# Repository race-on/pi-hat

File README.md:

Race On Pi HAT
=====

A Raspberry Pi HAT to control a self-driving car. HAT includes:
1. 3.5A DC-DC converter to power the Pi from a battery (2-3 LiPo cells)
2. 10A H-bridge for DC motor control
3. 3A LDO to power servo at 6V for faster response time
4. Battery alarm when the voltage drops under 6V
5. I2C accelerometer interface
6. Interface for encoders based on the QRE1113 analog line sensor
7. Compatible with Jetson Nano
8. Reverse polarity protection
9. Optimized for Seeed Studio PCBA

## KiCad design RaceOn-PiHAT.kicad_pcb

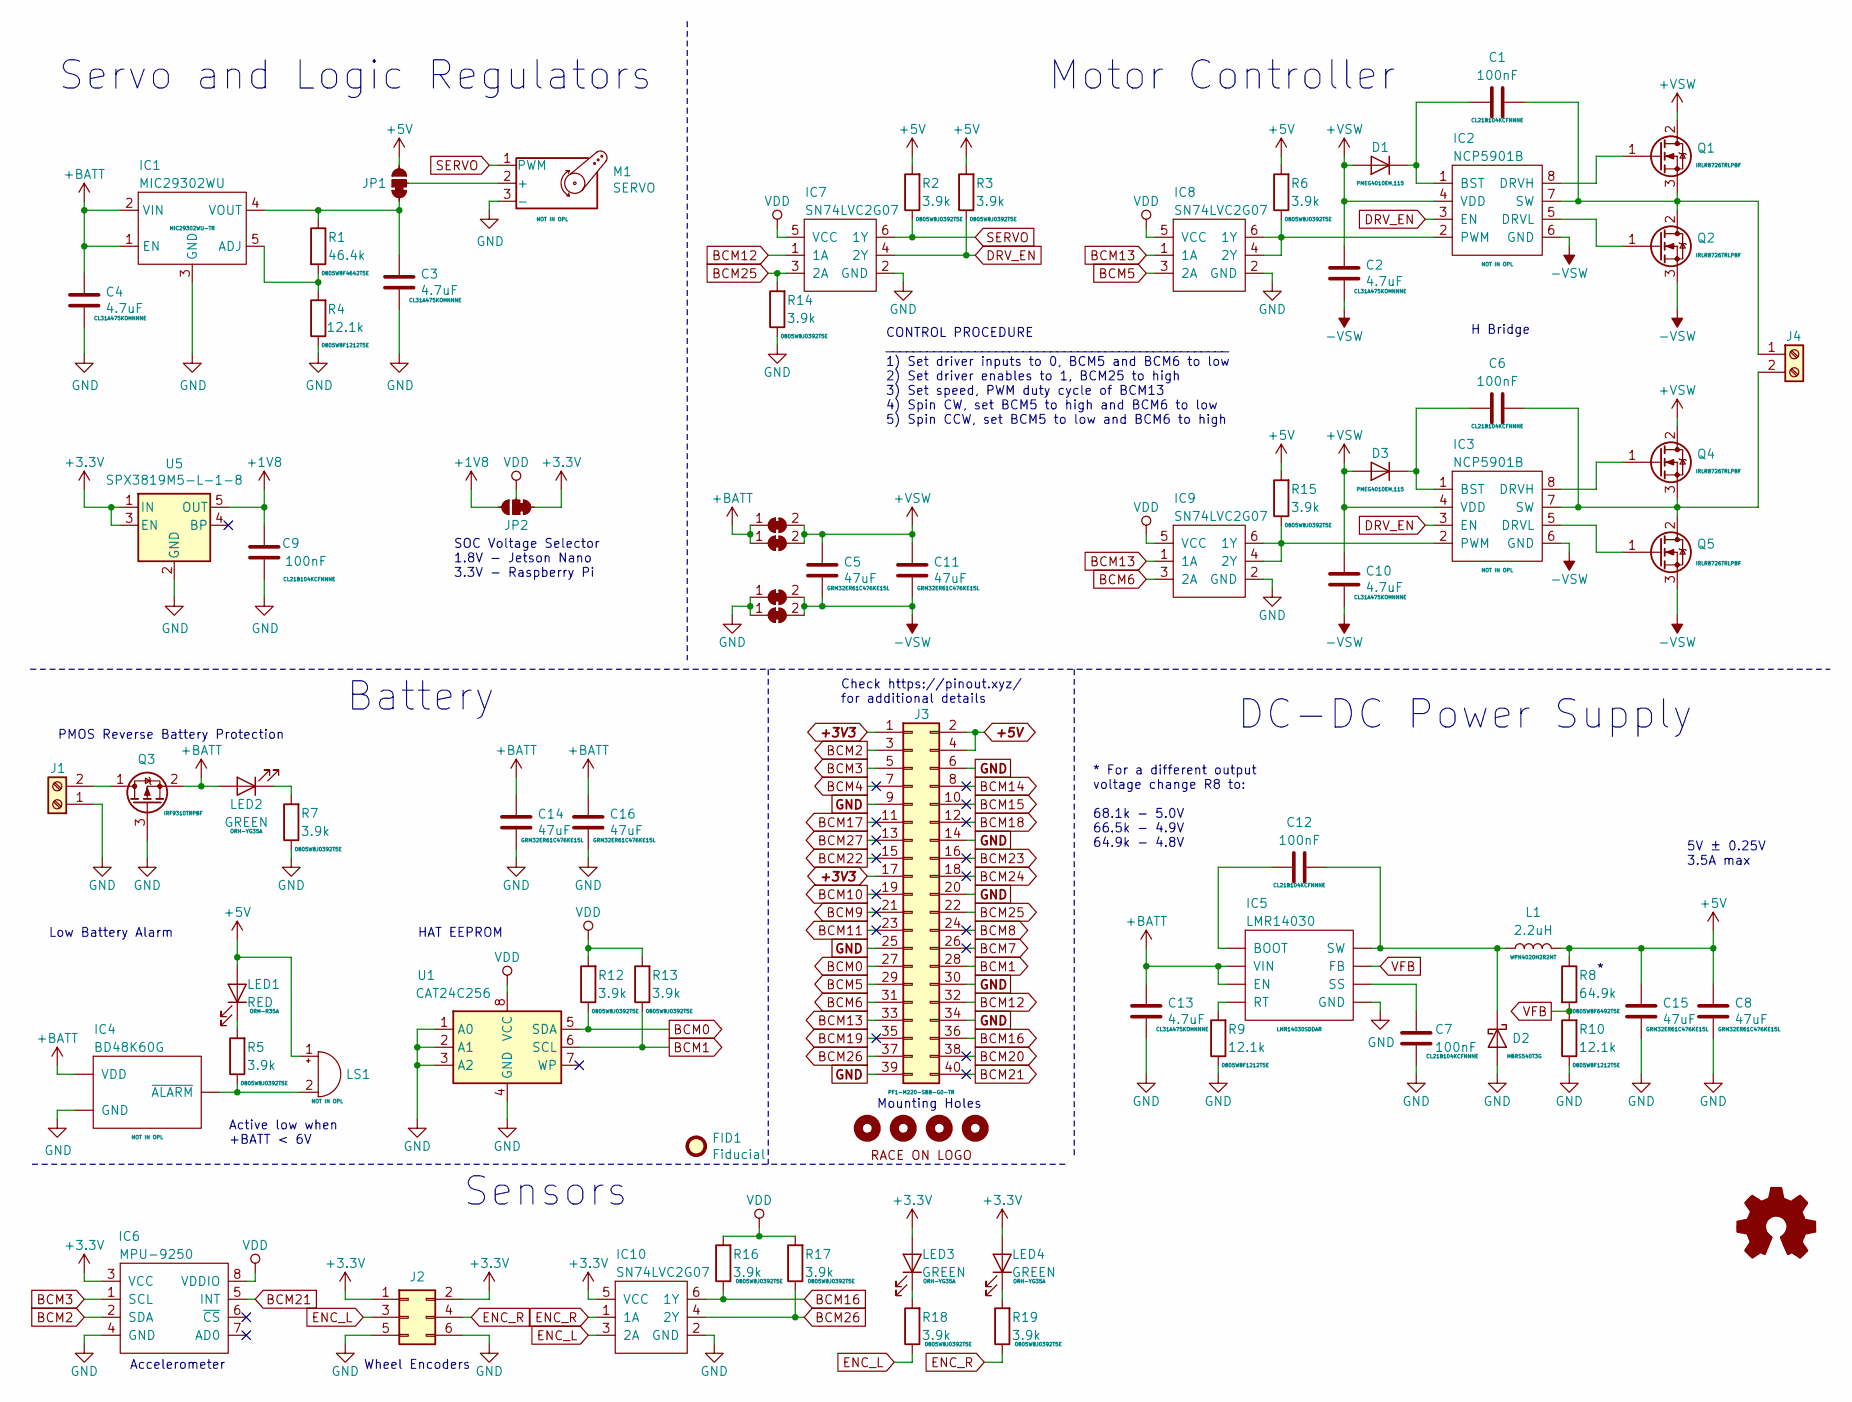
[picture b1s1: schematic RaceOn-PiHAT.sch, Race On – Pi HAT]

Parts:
C1, C6, C7, C9, C12: 100nF; CAPC200X125X95L45M; MPN CL21B104KCFNNNE
C2, C3, C4, C10, C13: 4.7uF; CAPC320X160X180L50M; MPN CL31A475KOHNNNE
C5, C8, C11, C14, C15, C16: 47uF; CAPC320X250X270L60M; MPN GRM32ER61C476KE15L
D1, D3: D; SOD350X160X120L45X62M; MPN PMEG4010EH,115
D2: D_Schottky; DIOM795X590X261L117X305M; MPN MBRS540T3G
FID1: Fiducial; FID1M3
H1, H2, H3, H4: MountingHole; MTGP620H275V8H50
IC1: MIC29302WU; DPAK6P67_587X190L89X29T300X275M; MPN MIC29302WU-TR
IC2, IC3: NCP5901B; SOIC8P127_490X600X175L83X42M; MPN NOT IN OPL
IC4: BD48K60G; SOT23-3P95_280X125L45X40M; MPN NOT IN OPL
IC5: LMR14030; SOIC9P127_490X600X170L83X41T287X202; MPN LMR14030SDDAR
IC6: MPU-9250; PGA28P254C7R4L1840X1127H200
IC7, IC8, IC9, IC10: SN74LVC2G07; SOT23-6P95_280X145L45X37M; MPN SN74LVC2G07DBVR
J1, J4: Screw_Terminal_01x02; TerminalBlock_Phoenix_PT-1,5-2-5.0-H_1x02_P5.00mm_Horizontal; MPN 1935161
J2: Conn_02x03_Odd_Even; HDRV6W65P254_3X2_762X508H900; MPN A2541WV-2x3P
J3: Pi Connector; RHDRV40W64P254_20X2_5120X500H850; MPN PF1-M220-SBB-G0-TR
JP1, JP2: SolderJumper; SJ3B12P10X15
JP3, JP4, JP5, JP6: SolderJumper_2_Bridged; SolderJumper-2_P1.3mm_Bridged_Pad1.0x1.5mm
L1: 2.2uH; INDM400X400X200L95X310M; MPN WPN4020H2R2MT
LED1: RED; LEDC197X125X85L45L; MPN ORH-R35A
LED2, LED3, LED4: GREEN; LEDC197X125X85L45L; MPN ORH-YG35A
LOGO1: RACEON-LOGO; RACEON
LOGO2: Logo_Open_Hardware_Small; OSHW-Logo2_7.3x6mm_SilkScreen
LS1: AI1027TWT5V2R; LSP500W60D980H500; MPN NOT IN OPL
M1: SERVO; HDRV3W64P254_3X1_762X254H854; MPN NOT IN OPL
Q1, Q2, Q4, Q5: IPD50R380CE; DPAK3P460_990X239L160X76T650X546L; MPN IRLR8726TRLPBF
Q3: SQJA37EP1; SOIC8P127_490X600X175L83X42M-TRANZISTOR; MPN IRF9310TRPBF
R1: 46.4k; RESC200X127X65L40M; MPN 0805W8F4642T5E
R2, R3, R5, R6, R7, R12, R13, R14, R15, R16, R17, R18, R19: 3.9k; RESC200X127X65L40M; MPN 0805W8J0392T5E
R4, R9, R10: 12.1k; RESC200X127X65L40M; MPN 0805W8F1212T5E
R8: 64.9k; RESC200X127X65L40M; MPN 0805W8F6492T5E
U1: CAT24C256; SOIC8P127_490X600X175L83X42M; MPN CAT24C256WI-GT3
U5: SPX3819M5-L-1-8; SOT23-5P95_280X145L45X40M; MPN SPX3819M5-L-1-8/TR

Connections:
+1V8: C9.2, JP2.3 (B), U5.5 (OUT)
+5V: C8.2, C15.2, J3.2, J3.4, JP1.3 (B), L1.1, LED1.2 (A), LS1.1 (-), R2.2, R3.2, R6.2, R8.1, R15.2
+BATT: C4.2, C13.2, C14.2, C16.2, IC1.1 (EN), IC1.2 (VIN), IC4.3 (VDD), IC5.2 (VIN), IC5.3 (EN), JP3.1 (A), JP4.1 (A), LED2.2 (A), Q3.2 (S)
+VSW: C2.2, C5.2, C10.2, C11.2, D1.2 (A), D3.2 (A), IC2.4 (VDD), IC3.4 (VDD), JP3.2 (B), JP4.2 (B), Q1.2 (D), Q4.2 (D)
-VSW: C2.1, C5.1, C10.1, C11.1, IC2.6 (GND), IC3.6 (GND), JP5.2 (B), JP6.2 (B), Q2.3 (S), Q5.3 (S)
BCM0: J3.27, R12.1, U1.5 (SDA)
BCM1: J3.28, R13.1, U1.6 (SCL)
BCM2: IC6.2 (SDA), J3.3
BCM3: IC6.1 (SCL), J3.5
BCM4: J3.7
BCM5: IC8.3 (2A), J3.29
BCM6: IC9.3 (2A), J3.31
BCM7: J3.26
BCM8: J3.24
BCM9: J3.21
BCM10: J3.19
BCM11: J3.23
BCM12: IC7.1 (1A), J3.32
BCM13: IC8.1 (1A), IC9.1 (1A), J3.33
BCM14: J3.8
BCM15: J3.10
BCM16: IC10.6 (1Y), J3.36, R16.1
BCM17: J3.11
BCM18: J3.12
BCM19: J3.35
BCM20: J3.38
BCM21: IC6.5 (INT), J3.40
BCM22: J3.15
BCM23: J3.16
BCM24: J3.18
BCM25: IC7.3 (2A), J3.22, R14.2
BCM26: IC10.4 (2Y), J3.37, R17.1
BCM27: J3.13
DRV_EN: IC2.3 (EN), IC3.3 (EN), IC7.4 (2Y), R3.1
ENC_L: IC10.3 (2A), J2.3, R18.1
ENC_R: IC10.1 (1A), J2.4, R19.1
GND: C3.1, C4.1, C7.1, C8.1, C9.1, C13.1, C14.1, C15.1, C16.1, D2.2 (A), IC1.3 (GND), IC1.6 (GND), IC4.1 (GND), IC5.7 (GND), IC5.9 (GND), IC6.4 (GND), IC7.2 (GND), IC8.2 (GND), IC9.2 (GND), IC10.2 (GND), J1.1, J2.5, J2.6, J3.6, J3.9, J3.14, J3.20, J3.25, J3.30, J3.34, J3.39, JP5.1 (A), JP6.1 (A), M1.3 (-), Q3.3 (G), R4.1, R7.1, R9.1, R10.1, R14.1, U1.1 (A0), U1.2 (A1), U1.3 (A2), U1.4 (GND), U5.2 (GND)
unnamed: C1.1, IC2.7 (SW), J4.1, Q1.3 (S), Q2.2 (D)
unnamed: C1.2, D1.1 (K), IC2.1 (BST)
unnamed: C3.2, IC1.4 (VOUT), JP1.1 (A), R1.1
unnamed: C6.1, IC3.7 (SW), J4.2, Q4.3 (S), Q5.2 (D)
unnamed: C6.2, D3.1 (K), IC3.1 (BST)
unnamed: C7.2, IC5.6 (SS)
unnamed: C12.1, D2.1 (K), IC5.8 (SW), L1.2
unnamed: C12.2, IC5.1 (BOOT)
unnamed: IC1.5 (ADJ), R1.2, R4.2
unnamed: IC2.2 (PWM), IC8.4 (2Y), IC8.6 (1Y), R6.1
unnamed: IC2.5 (DRVL), Q2.1 (G)
unnamed: IC2.8 (DRVH), Q1.1 (G)
unnamed: IC3.2 (PWM), IC9.4 (2Y), IC9.6 (1Y), R15.1
unnamed: IC3.5 (DRVL), Q5.1 (G)
unnamed: IC3.8 (DRVH), Q4.1 (G)
unnamed: IC4.2 (~ALARM), LS1.2 (+), R5.1
unnamed: IC5.4 (RT), R9.2
unnamed: J1.2, Q3.1 (D)
unnamed: JP1.2 (C), M1.2 (+)
unnamed: LED1.1 (K), R5.2
unnamed: LED2.1 (K), R7.2
unnamed: LED3.1 (K), R18.2
unnamed: LED4.1 (K), R19.2
SERVO: IC7.6 (1Y), M1.1 (PWM), R2.1
VDD: IC6.8 (VDDIO), IC7.5 (VCC), IC8.5 (VCC), IC9.5 (VCC), JP2.2 (C), R12.2, R13.2, R16.2, R17.2, U1.8 (VCC)
VFB: IC5.5 (FB), R8.2, R10.2

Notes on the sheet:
DC-DC Power Supply
5V ± 0.25V 3.5A max
Motor Controller
Low Battery Alarm
* For a different output voltage change R8 to: 68.1k - 5.0V 66.5k - 4.9V 64.9k - 4.8V
Servo and Logic Regulators
H Bridge
SOC Voltage Selector 1.8V - Jetson Nano 3.3V - Raspberry Pi
Sensors
Accelerometer
Wheel Encoders
Check https://pinout.xyz/ for additional details
Mounting Holes
PMOS Reverse Battery Protection
HAT EEPROM
CONTROL PROCEDURE __________________________________________________ 1) Set driver inputs to 0, BCM5 and BCM6 to low 2) Set driver enables to 1, BCM25 to high 3) Set speed, PWM duty cycle of BCM13 4) Spin CW, set BCM5 to high and BCM6 to low 5) Spin CCW, set BCM5 to low and BCM6 to high
Battery
Active low when +BATT < 6V

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
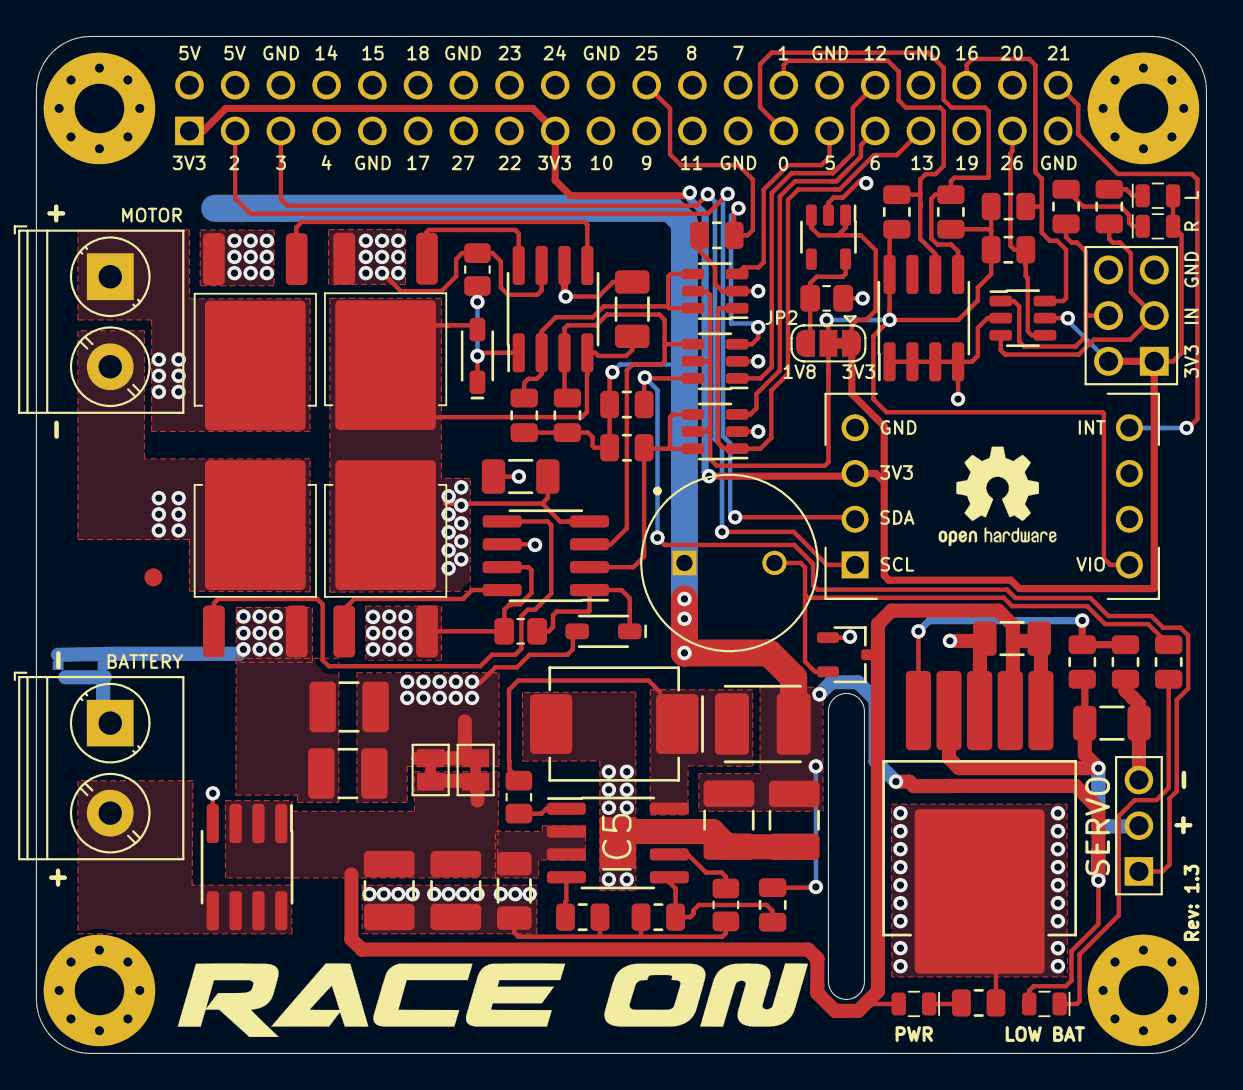
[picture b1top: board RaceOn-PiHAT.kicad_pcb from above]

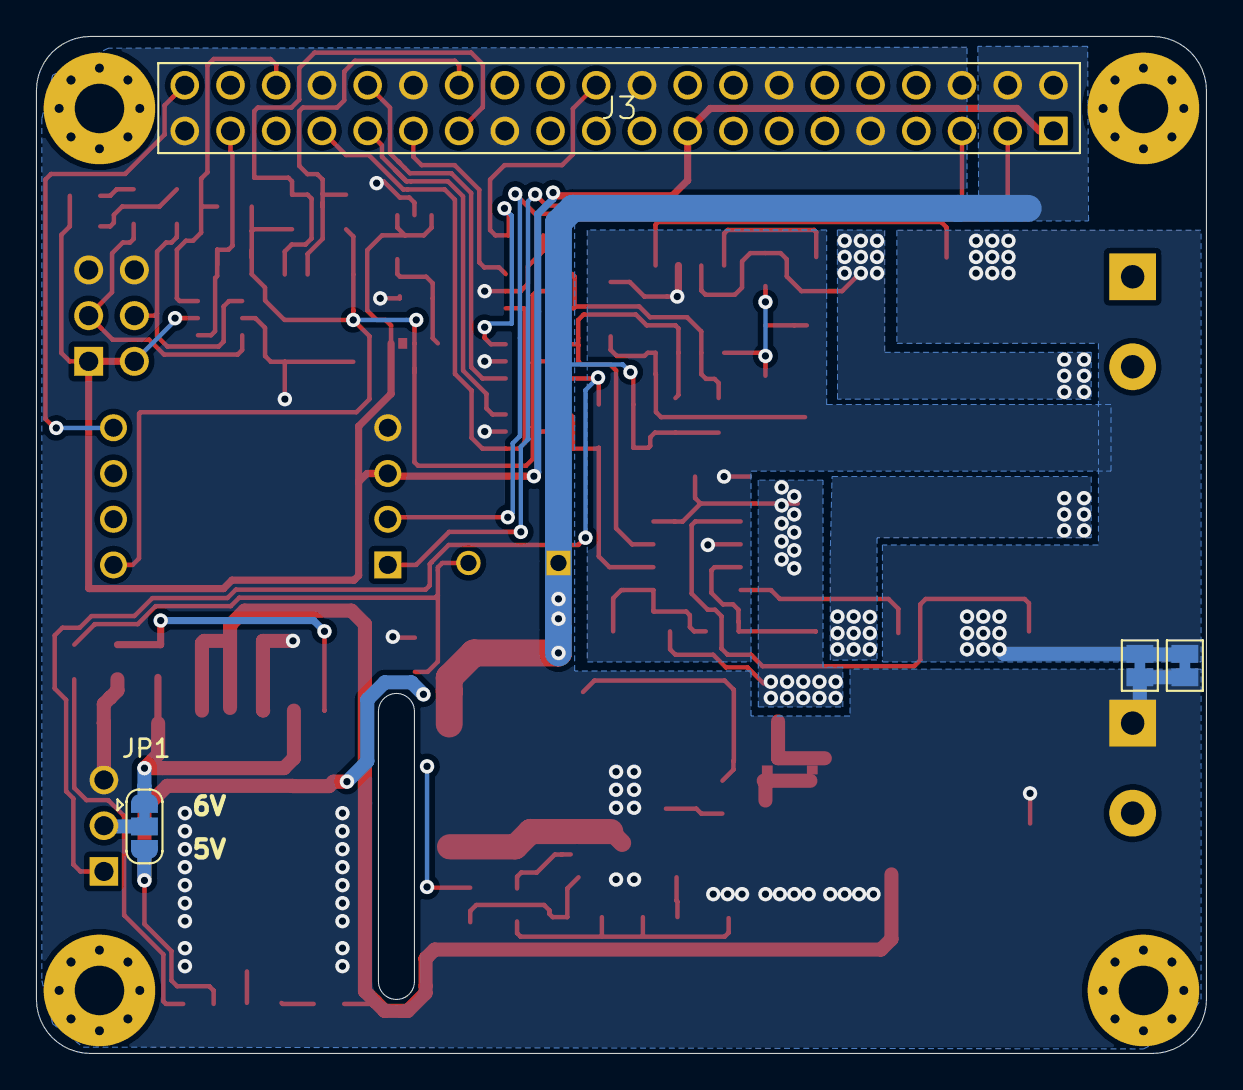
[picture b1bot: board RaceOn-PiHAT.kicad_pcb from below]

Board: 2 copper layers, 65.0 x 56.5 mm, 78 parts (4 on the bottom side), 48 nets.

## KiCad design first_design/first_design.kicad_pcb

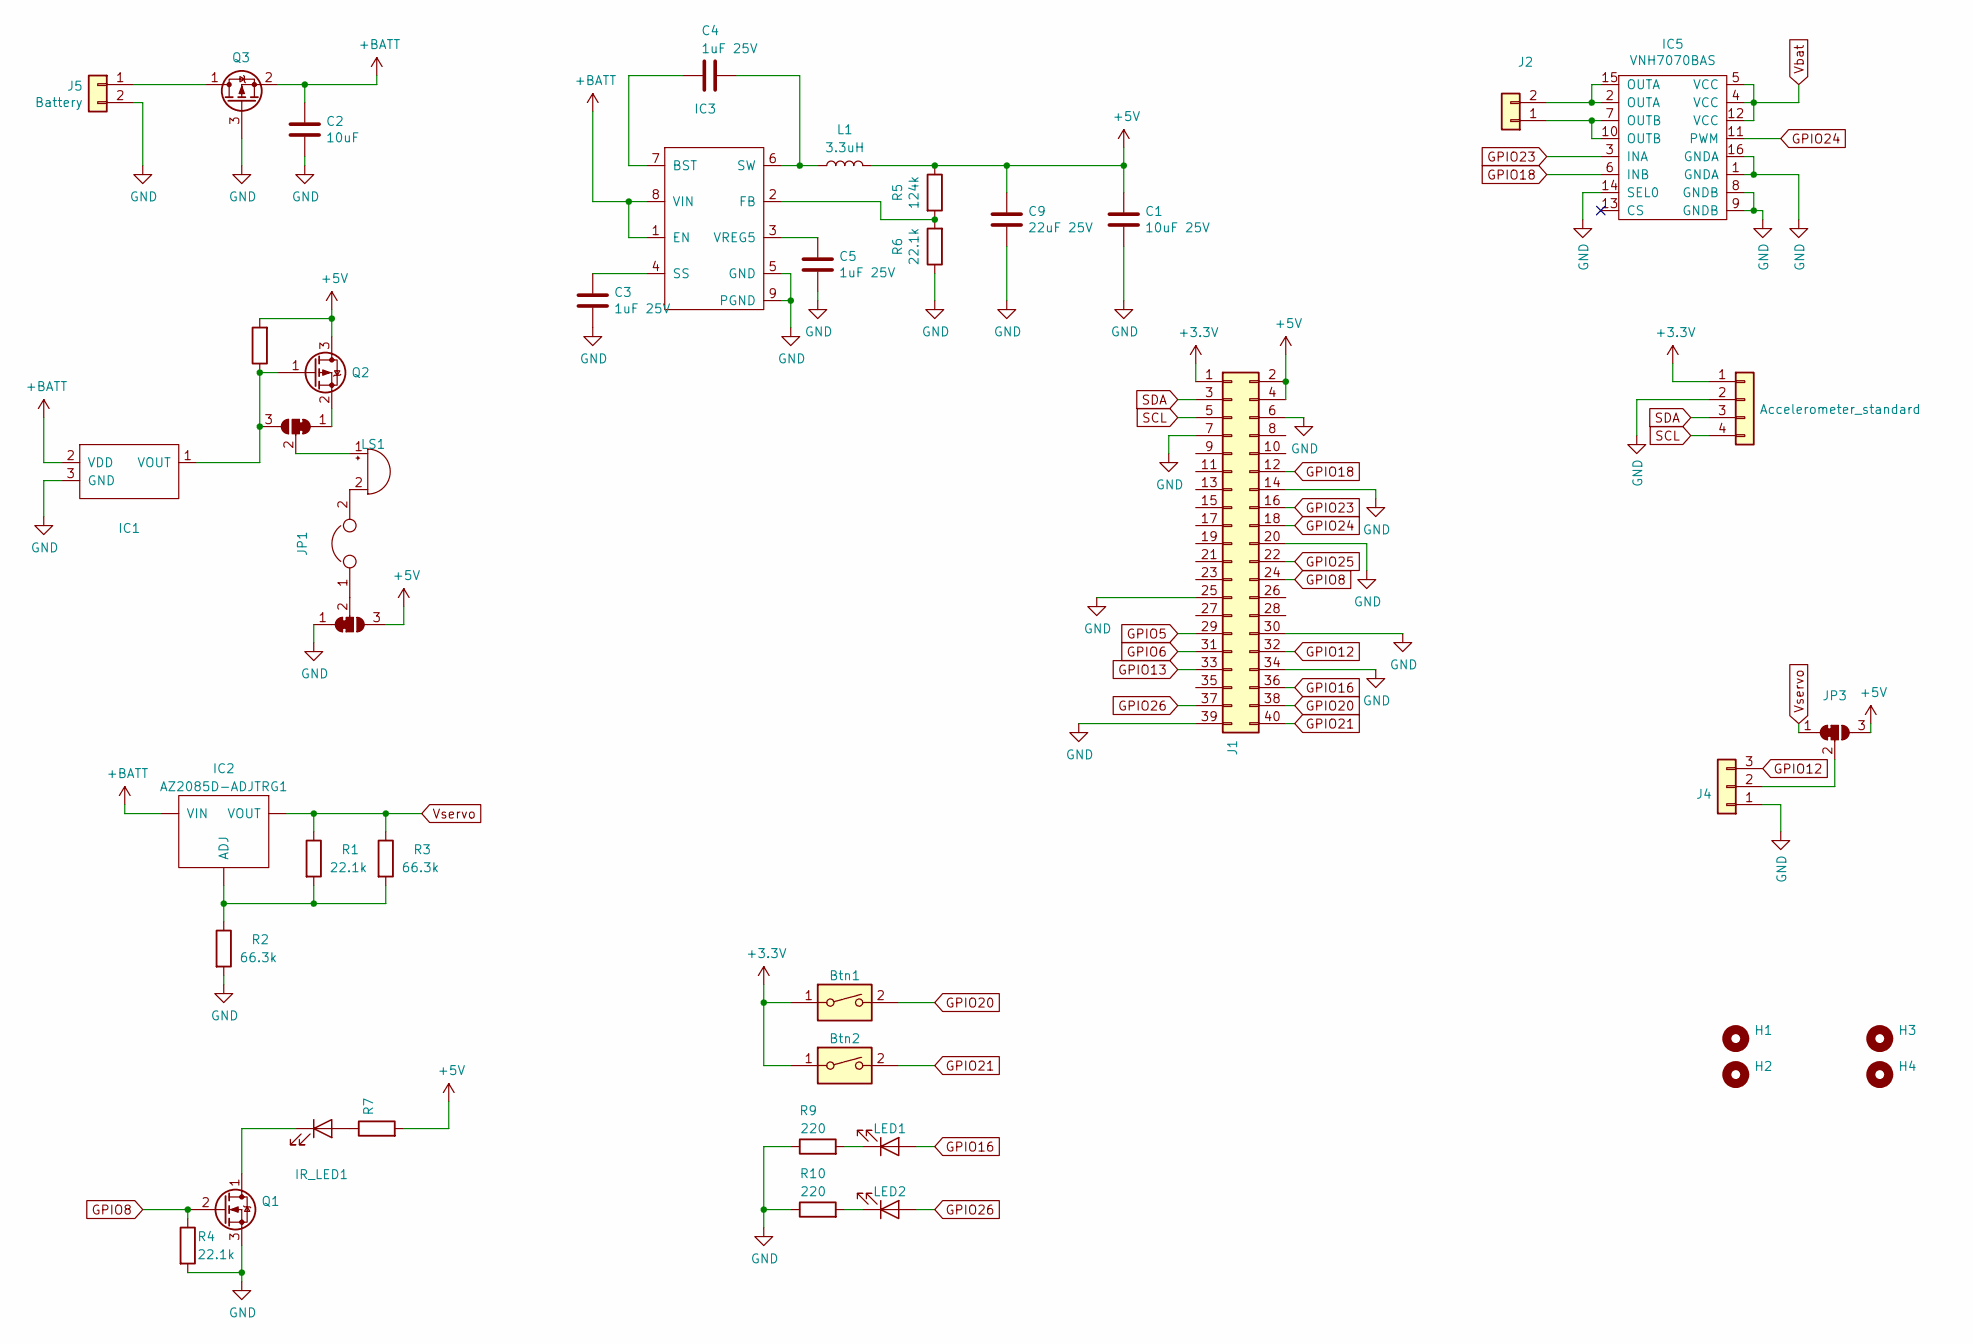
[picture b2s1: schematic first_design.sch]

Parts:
Btn1, Btn2: PTS636
C1: 10uF 25V; CAPC320X160X180L50M
C2: 10uF; RLC_EIA_3216
C3, C4, C5: 1uF 25V; CAPC320X160X180L50M
C9: 22uF 25V; CAPC320X250X180L50L
H1, H2, H3, H4: MountingHole; MountingHole_2.7mm_M2.5
IC1: BD48K60; SSOP3
IC2: AZ2085D-ADJTRG1; TO252-2
IC3: AP65450; SOIC9P127_490X600X150L72X40T305X241L
IC5: VNH7070BAS; SOIC16P127_990X600X175L83X41M
IR_LED1: IR_LED; LED_YSL-R531R3D-D2
J1: Conn_02x20_Odd_Even; RasPi_Header_0.9
J2: Conn_01x02; Connector_pads
J3: Accelerometer_standard
J4: Servo_motor; servo_connector
J5: Battery; Connector_pads
JP1: Jumper; standard_jumper
JP2, JP3, JP4: SolderJumper_3_Bridged12; SolderJumper-3_P1.3mm_Open_RoundedPad1.0x1.5mm_NumberLabels
L1: 3.3uH; INDC800X800X450L240M
LED1, LED2: 599-0210-007F; RLC_EIA_3216
LS1: AI1027TWT5V2R; Buzzer_AI1027TWT5V2R
Q1: 2N7002K; SOT23
Q2: DMG2301L-7; SOT23
Q3: SQJA37EP1; SO-8L
R1, R4, R6: 22.1k; RLC_EIA_3216
R2, R3: 66.3k; RLC_EIA_3216
R5: 124k; RLC_EIA_3216
R7, R8, R9, R10: 220; RLC_EIA_3216

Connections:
+3V3: Btn1.1, Btn2.1, J1.1, J3.1
+5V: C1.2, C9.2, J1.2, J1.4, JP3.3 (B), JP4.3 (B), L1.1, Q2.3 (D), R5.1, R7.2, R8.2
+BATT: C2.2, IC1.2 (VDD), IC2.3 (VIN), IC3.1 (EN), IC3.8 (VIN), Q3.2 (S)
GND: C1.1, C2.1, C3.1, C5.1, C9.1, IC1.3 (GND), IC3.5 (GND), IC3.9 (PGND), IC5.1 (GNDA), IC5.8 (GNDB), IC5.9 (GNDB), IC5.14 (SEL0), IC5.16 (GNDA), J1.6, J1.7, J1.14, J1.20, J1.25, J1.30, J1.34, J1.39, J3.2, J4.1, J5.2, JP4.1 (A), Q1.3 (S), Q3.3 (G), R2.2, R4.2, R6.1, R9.1, R10.1
GPIO5: J1.29
GPIO6: J1.31
GPIO8: J1.24, Q1.2 (G), R4.1
GPIO12: J1.32, J4.3
GPIO13: J1.33
GPIO16: J1.36, LED1.2 (A)
GPIO18: IC5.6 (INB), J1.12
GPIO20: Btn1.2, J1.38
GPIO21: Btn2.2, J1.40
GPIO23: IC5.3 (INA), J1.16
GPIO24: IC5.11 (PWM), J1.18
GPIO25: J1.22
GPIO26: J1.37, LED2.2 (A)
unnamed: C3.2, IC3.4 (SS)
unnamed: C4.1, IC3.6 (SW), L1.2
unnamed: C4.2, IC3.7 (BST)
unnamed: C5.2, IC3.3 (VREG5)
unnamed: IC1.1 (VOUT), JP2.3 (B), Q2.1 (G), R8.1
unnamed: IC2.1 (ADJ), R1.2, R2.1, R3.2
unnamed: IC3.2 (FB), R5.2, R6.2
unnamed: IC5.7 (OUTB), IC5.10 (OUTB), J2.1
unnamed: IC5.2 (OUTA), IC5.15 (OUTA), J2.2
unnamed 27: IR_LED1.1 (K), Q1.1 (D); also elsewhere on the board
unnamed 28: IR_LED1.2 (A), R7.1; also elsewhere on the board
unnamed: J4.2, JP3.2 (C)
unnamed: J5.1, Q3.1 (D)
unnamed: JP1.1, JP4.2 (C)
unnamed: JP1.2, LS1.2 (+)
unnamed: JP2.1 (A), Q2.2 (S)
unnamed: JP2.2 (C), LS1.1 (-)
unnamed: LED1.1 (K), R9.2
unnamed: LED2.1 (K), R10.2
SCL: J1.5, J3.4
SDA: J1.3, J3.3
Vbat: IC5.4 (VCC), IC5.5 (VCC), IC5.12 (VCC)
Vservo: IC2.2 (VOUT), JP3.1 (A), R1.1, R3.1

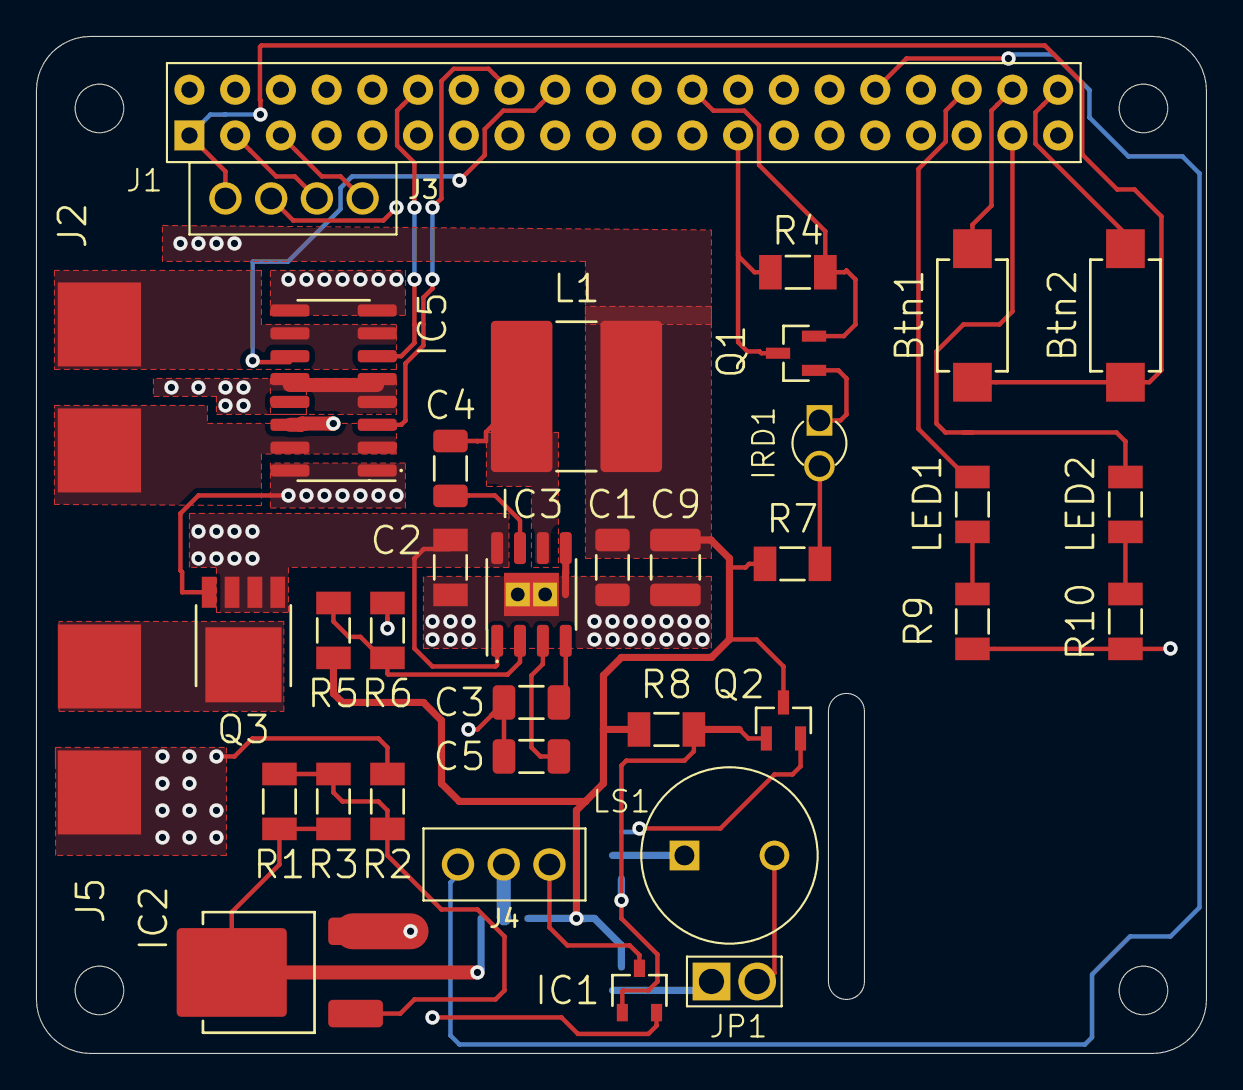
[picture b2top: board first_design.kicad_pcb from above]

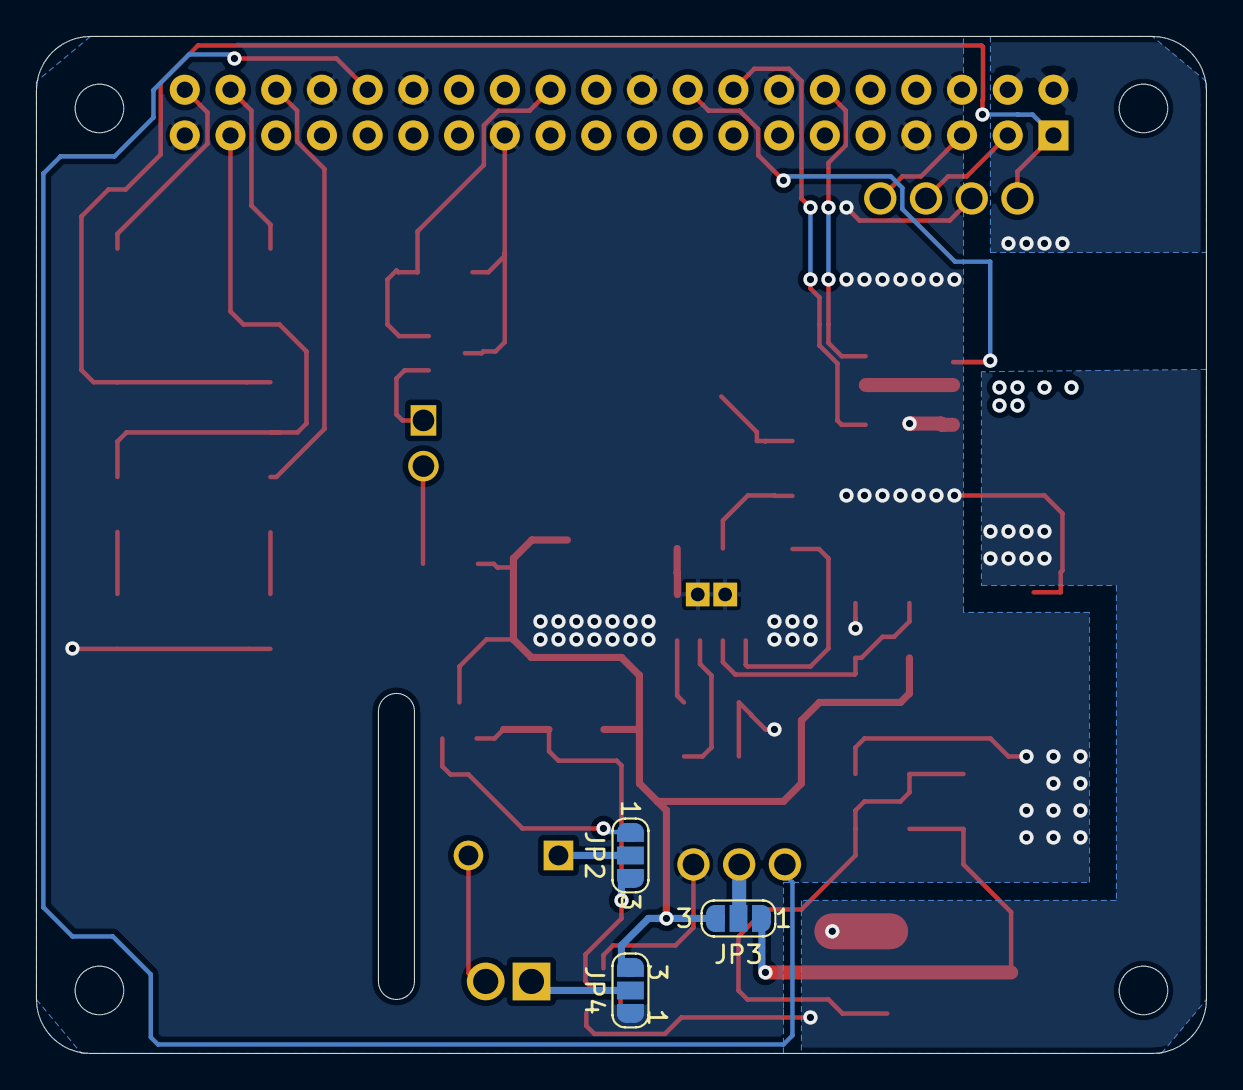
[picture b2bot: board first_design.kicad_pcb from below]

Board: 2 copper layers, 65.0 x 56.5 mm, 43 parts (3 on the bottom side), 36 nets.

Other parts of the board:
IRD1: IR_LED; LED_YSL-R531R3D-D2

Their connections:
unnamed 27: IRD1.1; also elsewhere on the board
unnamed 28: IRD1.2; also elsewhere on the board

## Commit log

2019-07-03 labels added
2019-07-08 buzzer layout + buttons added
2019-07-09 IR Circuit added
2019-07-09 IR circuit fix
2019-07-10 ldo added
2019-07-11 footprint-libraries added
2019-07-11 updating footprints
2019-07-11 edge cut added
2019-07-12 footprints added
2019-07-13 some connectors footprints added
2019-07-13 raspberry pin headers added for review
2019-07-13 motor & power connector pending changes
2019-07-13 working on PCB design
2019-07-14 PCB Board first layout
2019-07-14 PCB board in the works
2019-07-16 playing with PiHat footprint
2019-07-16 fitting components in piHat
2019-07-16 Night Session
2019-07-16 board
2019-07-17 tracing
2019-07-18 traced buck
2019-07-18 Stuck trying to trace Pi connector pins. Need some tips
2019-07-20 Before changes
2019-07-22 working on tracing, back layer is messed up
2019-07-22 Killing it
2019-07-22 Everything is wired, fixed schematic, haven't found PMOS and IR yet. Check PCB design
2019-07-23 final touches
2019-07-23 final final touches
2019-07-23 schematic edit
2019-07-23 still finalizing
2019-07-25 Ready for PCB Prototyping
2019-08-03 Remove extra components after playing with the first prototype
2019-08-03 Add to do list for the next prototyp
2019-08-09 Before deleting old motor controller
2019-08-09 Late night commit for schematic
2019-08-09 Renamed project to RaceOn-PiHAT
2019-08-09 Renamed the project
2019-08-10 Included all parts in the schematic
2019-08-12 Assign OPL number to each part to be assembled
2019-08-14 Add footprints for all parts
2019-08-16 Ordered from Seeed PCBA
2019-12-01 Version 2
2019-12-12 Production
2019-12-20 Latest version
2019-12-22 Partial fix
2019-12-22 Reverded to production board
2019-12-22 Update .gitignore for KiCAD projects
2019-12-22 Reposition IMU and fix labels
2019-12-23 Remove EMI filter, replace low ESR caps with ceramic
2019-12-23 Labeled motor and battery connectors
2019-12-23 Finished board
2019-12-23 Add new footprint for the DC-DC IC
2019-12-24 Rev 1.3 final
2019-12-24 Clean repo from old files
2019-12-24 Add schematic image
